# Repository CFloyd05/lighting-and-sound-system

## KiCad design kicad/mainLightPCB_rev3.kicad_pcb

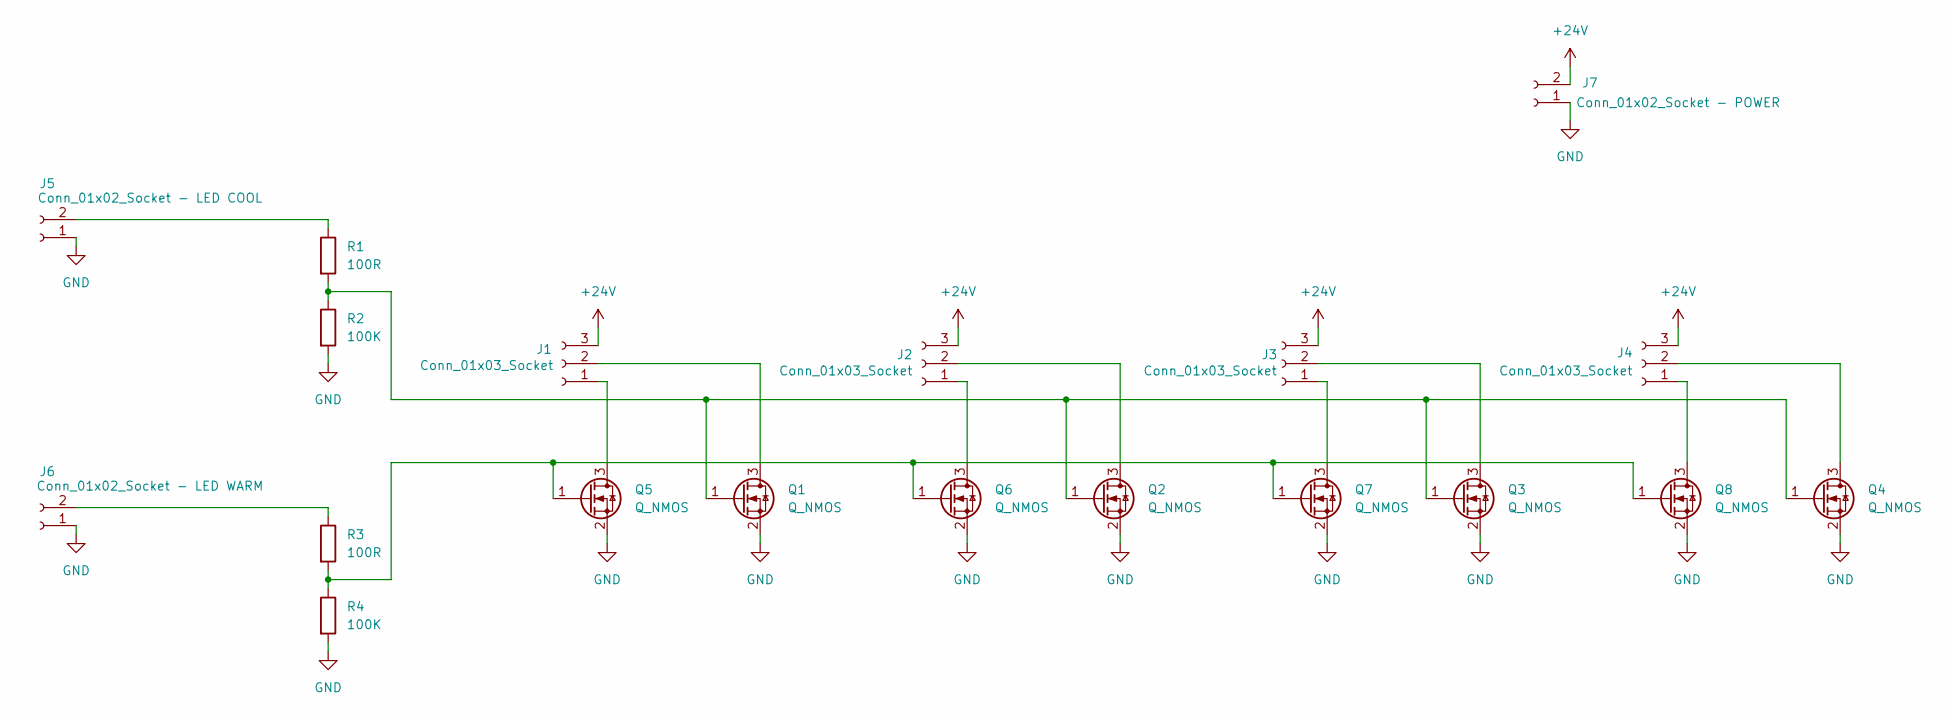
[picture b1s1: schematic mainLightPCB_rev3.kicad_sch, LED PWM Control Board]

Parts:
J1, J2, J3, J4: Conn_01x03_Socket; TerminalBlock_bornier-3_P5.08mm
J5: Conn_01x02_Socket - LED COOL; JST_XH_B2B-XH-A_1x02_P2.50mm_Vertical
J6: Conn_01x02_Socket - LED WARM; JST_XH_B2B-XH-A_1x02_P2.50mm_Vertical
J7: Conn_01x02_Socket - POWER; TerminalBlock_bornier-2_P5.08mm
Q1, Q2, Q3, Q4, Q5, Q6, Q7, Q8: Q_NMOS; SOT-23
R1, R3: 100R; R_0603_1608Metric_Pad0.98x0.95mm_HandSolder
R2, R4: 100K; R_0603_1608Metric_Pad0.98x0.95mm_HandSolder

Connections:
+24V: J1.3, J2.3, J3.3, J4.3, J7.2
GND: J5.1, J6.1, J7.1, Q1.2 (S), Q2.2 (S), Q3.2 (S), Q4.2 (S), Q5.2 (S), Q6.2 (S), Q7.2 (S), Q8.2 (S), R2.2, R4.2
unnamed: J1.1, Q5.3 (D)
unnamed: J1.2, Q1.3 (D)
unnamed: J2.1, Q6.3 (D)
unnamed: J2.2, Q2.3 (D)
unnamed: J3.1, Q7.3 (D)
unnamed: J3.2, Q3.3 (D)
unnamed: J4.1, Q8.3 (D)
unnamed: J4.2, Q4.3 (D)
unnamed: J5.2, R1.1
unnamed: J6.2, R3.1
unnamed: Q1.1 (G), Q2.1 (G), Q3.1 (G), Q4.1 (G), R1.2, R2.1
unnamed: Q5.1 (G), Q6.1 (G), Q7.1 (G), Q8.1 (G), R3.2, R4.1

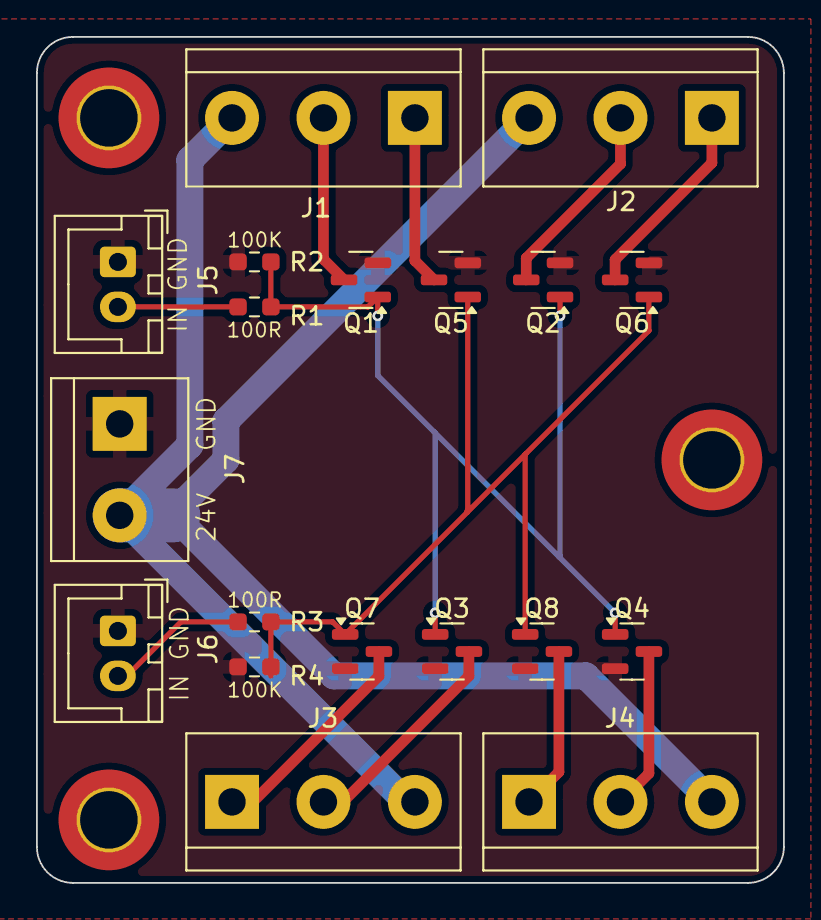
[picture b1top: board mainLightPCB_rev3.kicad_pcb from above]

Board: 2 copper layers, 41.5 x 47.0 mm, 19 parts (0 on the bottom side), 14 nets.
